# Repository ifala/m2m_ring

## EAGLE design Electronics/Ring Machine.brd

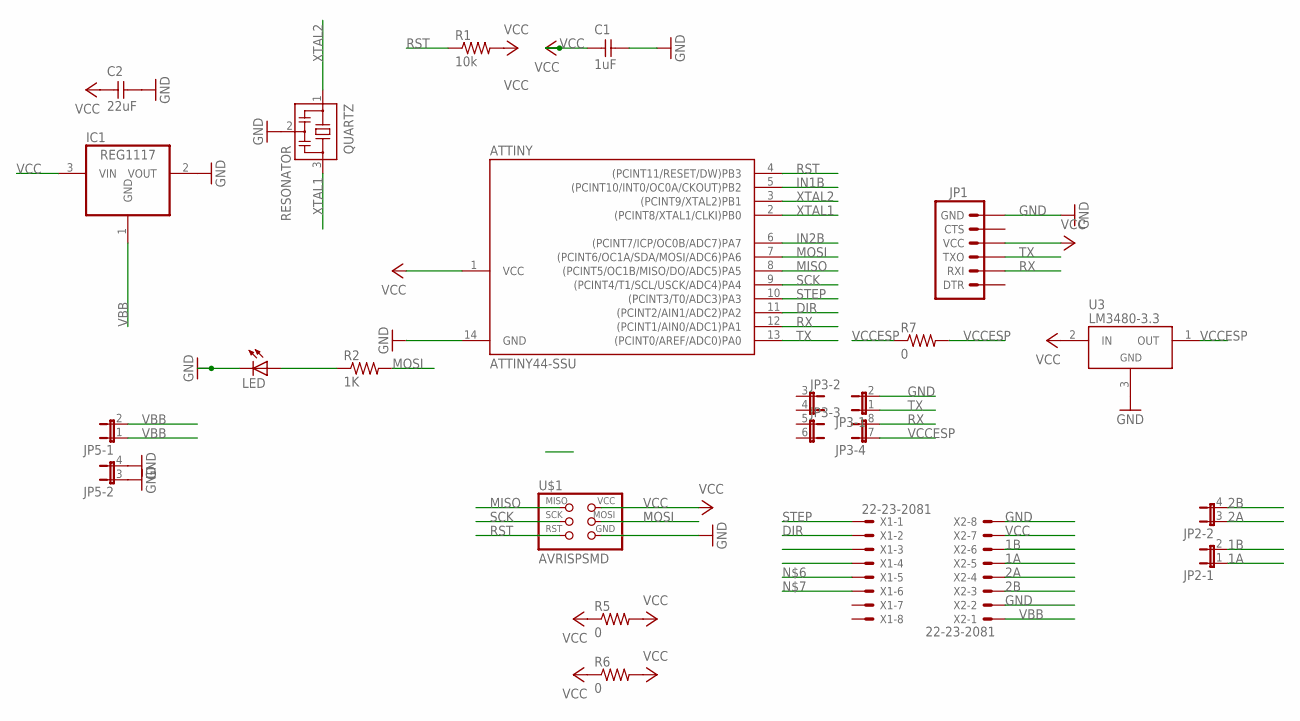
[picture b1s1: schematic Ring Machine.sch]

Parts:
ATTINY: ATTINY44-SSU; SOIC14
C1: 1uF; 1206
C2: 22uF; 1206
IC1: REG1117; SOT223
JP1: ARDUINO_SERIAL_PROGRAMLONGPADS; 1X06_LONGPADS
JP2, JP5: JP2QE; JP2Q
JP3: JP4QE; JP4Q
LED: LED1206; 1206
QUARTZ: RESONATOR; EFOBM
R1: 10k; 1206
R2: 1K; 1206
R5, R6, R7: 0; 1206
U3: LM3480-3.3; SOT-23-3
U$1: AVRISPSMD; 2X03SMD
X1, X2: 22-23-2081

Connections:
1A: JP2.1, X2.5
1B: JP2.2, X2.6
2A: JP2.3 (1), X2.4
2B: JP2.4 (2), X2.3
DIR: ATTINY.11 ((PCINT2/AIN1/ADC2)PA2), X1.2
GND: ATTINY.14 (GND), C1.2, C2.2, IC1.2 (VOUT), JP1.6 (GND), JP3.2, JP5.3 (1), JP5.4 (2), LED.2 (C), QUARTZ.2, U3.3 (GND), U$1.6 (GND), X2.2, X2.8
IN1B: ATTINY.5 ((PCINT10/INT0/OC0A/CKOUT)PB2)
IN2B: ATTINY.6 ((PCINT7/ICP/OC0B/ADC7)PA7)
LEDRES: LED.1 (A), R2.1
MISO: ATTINY.8 ((PCINT5/OC1B/MISO/DO/ADC5)PA5), U$1.1 (MISO)
MOSI: ATTINY.7 ((PCINT6/OC1A/SDA/MOSI/ADC6)PA6), R2.2, U$1.4 (MOSI)
RST: ATTINY.4 ((PCINT11/RESET/DW)PB3), R1.1, U$1.5 (RST)
RX: ATTINY.12 ((PCINT1/AIN0/ADC1)PA1), JP1.2 (RXI), JP3.8 (2)
SCK: ATTINY.9 ((PCINT4/T1/SCL/USCK/ADC4)PA4), U$1.3 (SCK)
STEP: ATTINY.10 ((PCINT3/T0/ADC3)PA3), X1.1
TX: ATTINY.13 ((PCINT0/AREF/ADC0)PA0), JP1.3 (TXO), JP3.1
VBB: IC1.1 (GND), JP5.1, JP5.2, X2.1
VCC: ATTINY.1 (VCC), C1.1, C2.1, IC1.3 (VIN), JP1.4 (VCC), R1.2, R5.1, R5.2, R6.1, R6.2, U3.2 (IN), U$1.2 (VCC), X2.7
VCCESP: JP3.7 (1), R7.1, R7.2, U3.1 (OUT)
XTAL1: ATTINY.2 ((PCINT8/XTAL1/CLKI)PB0), QUARTZ.3
XTAL2: ATTINY.3 ((PCINT9/XTAL2)PB1), QUARTZ.1

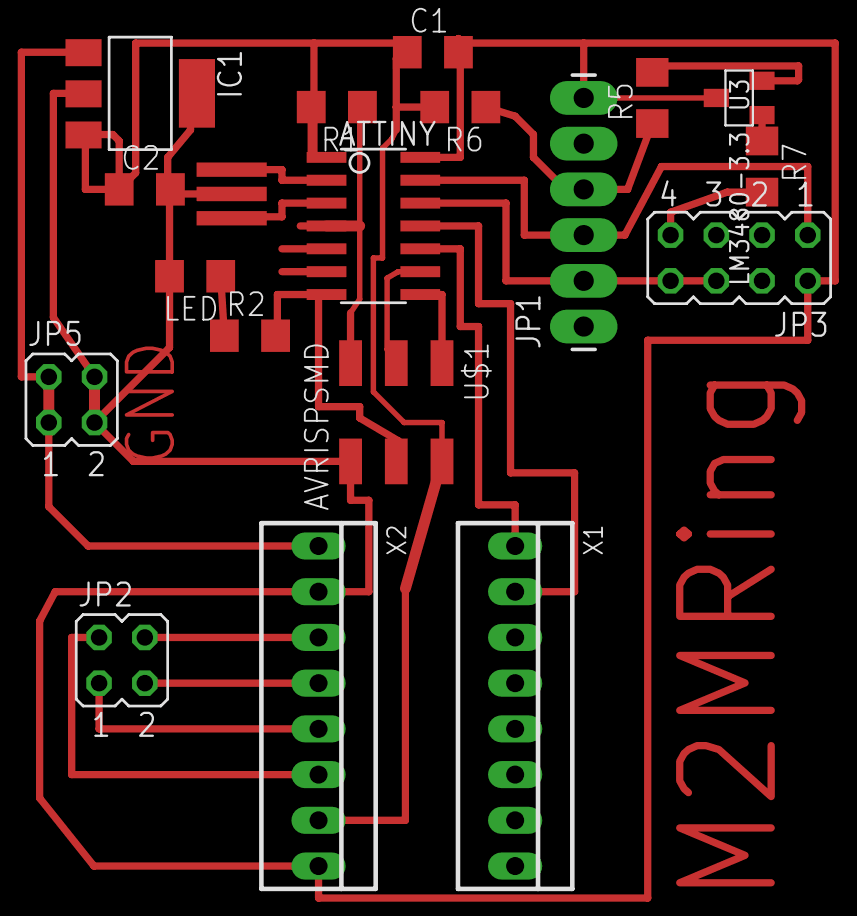
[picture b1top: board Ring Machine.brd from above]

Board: 2 copper layers, 19 parts (0 on the bottom side), 19 nets.

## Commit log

2015-05-27 1_upload
2015-06-12 y carriage and dxf file
2015-06-18 Electronics
2015-06-18 update 5mm
2015-06-19 5v regulator electronics
2015-06-30 final push
2015-06-30 ver1.3

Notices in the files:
parts and their libraries:
SparkFun-Connectors: Licensing: Creative Commons ShareAlike 4.0 International - https://creativecommons.org/licenses/by-sa/4.0
